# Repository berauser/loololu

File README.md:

# Dependencies

The project loolou depends on the avr-gcc and avrdude.

## Ubuntu

```
$ sudo apt-get install gcc-avr avrdude
```

# Build
## compile

```
$ make
```

## clean
```
$ make clean
```

## flash to attiny2313

```
# use default
# programmer: avrispv2
# usb device: /dev/ttyACM0
$ sudo make burn
```

```
# overwrite defaults
# AVRDUDE_PROGRAMMER override programmer type
# AVRDUDE_PORT overrides usb device
$ sudo make AVRDUDE_PROGRAMMER=avrispv2 AVRDUDE_PORT=/dev/ttyACM0 burn
```

## Useful links

* https://startingelectronics.org/tutorials/AVR-8-microcontrollers/ATtiny2313-tutorial/
* http://www.atmel.com/webdoc/avrlibcreferencemanual/index.html
* http://www.avr-tutorials.com/interrupts/avr-external-interrupt-c-programming

## Datasheet
### Attiny2313

* http://www.atmel.com/Images/Atmel-2543-AVR-ATtiny2313_Datasheet.pdf

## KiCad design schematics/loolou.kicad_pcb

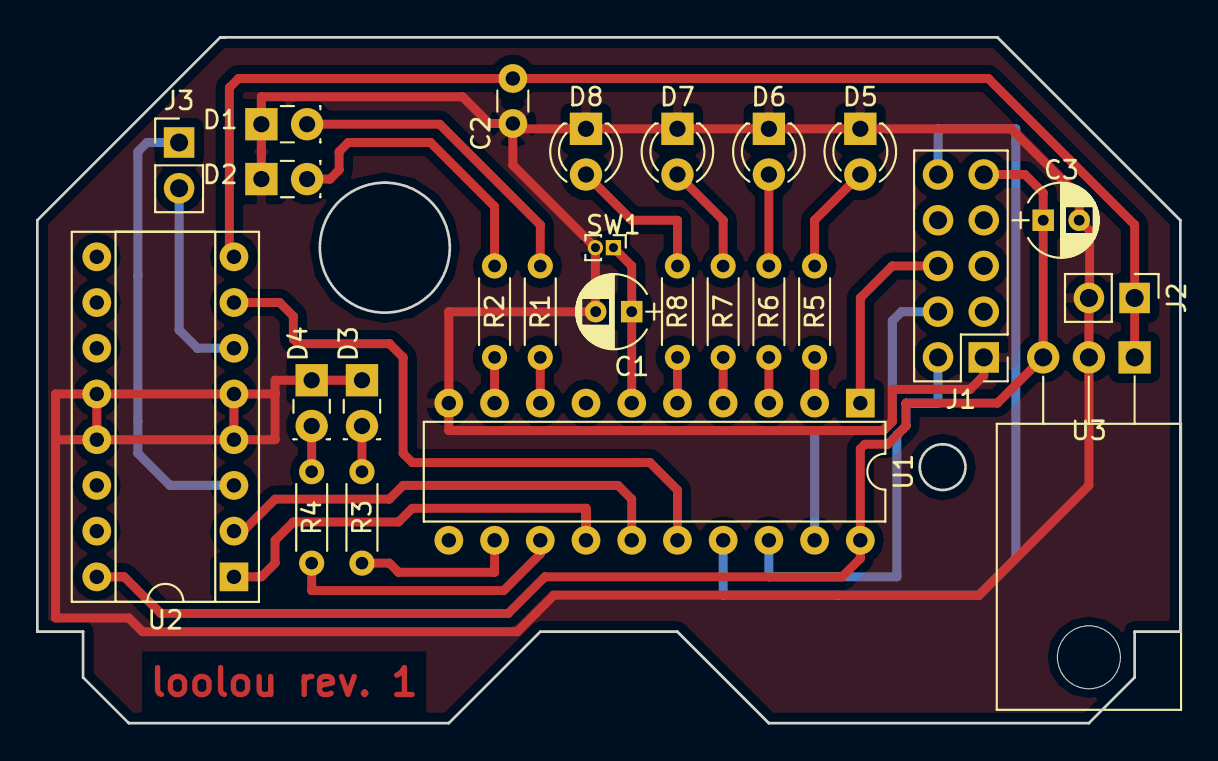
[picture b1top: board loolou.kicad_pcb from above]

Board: 2 copper layers, 63.5 x 38.1 mm, 26 parts (0 on the bottom side), 29 nets.

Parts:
C1, C3: 2,2uF; CP_Radial_D4.0mm_P2.00mm
C2: 0,1uF; C_Disc_D3.0mm_W1.6mm_P2.50mm
D1, D2, D3, D4: LED; LED_Rectangular_W3.9mm_H1.9mm
D5, D6, D7, D8: LED; LED_D3.0mm
J1: CONN_02X05; Pin_Header_Straight_2x05_Pitch2.54mm
J2, J3: Conn_01x02; Pin_Header_Straight_1x02_Pitch2.54mm
R1, R2, R3, R4: 68; R_Axial_DIN0204_L3.6mm_D1.6mm_P5.08mm_Horizontal
R5, R6, R7, R8: 120; R_Axial_DIN0204_L3.6mm_D1.6mm_P5.08mm_Horizontal
SW1: SW_Push; Pin_Header_Straight_1x02_Pitch1.00mm
U1: ATTINY2313-20PU; DIP-20_W7.62mm
U2: L293D; DIP-16_W7.62mm_Socket
U3: LF50CV; TO-220_Horizontal

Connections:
+9V: C2.1, J2.1, U2.8, U3.1
/BACKWARD: U1.16, U2.7
/BUTTON: C1.1, SW1.1, U1.6
/FORWARD: U1.15, U2.2
/LED_1: R5.1, U1.2
/LED_2: R6.1, U1.3
/LED_3: R7.1, U1.4
/LED_4: R8.1, U1.5
/LED_BLUE: R2.1, U1.9
/LED_GREEN: R3.1, U1.12
/LED_RED: R1.1, U1.8
/LED_YELLOW: R4.1, U1.13
/MISO: J1.2, U1.18
/MOSI: J1.10, U1.17
/MOTOR_A: J3.1, U2.3
/MOTOR_B: J3.2, U2.6
/PWM: U1.14, U2.1
/RESET: J1.6, U1.1
/SCK: J1.4, U1.19
GND: C1.2, C2.2, C3.2, D1.1, D2.1, D3.1, D4.1, D5.1, D6.1, D7.1, D8.1, J1.1, J2.2, SW1.2, U1.10, U2.4, U2.5, U2.12, U2.13, U3.2
unnamed: D1.2, R1.2
unnamed: D2.2, R2.2
unnamed: D3.2, R3.2
unnamed: D4.2, R4.2
unnamed: D5.2, R5.2
unnamed: D6.2, R6.2
unnamed: D7.2, R7.2
unnamed: D8.2, R8.2
VCC: C3.1, J1.9, U1.20, U2.16, U3.3

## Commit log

2017-08-18 change random speed calculation
2017-08-18 add simple readme
2017-10-27 change motor direction to fix the issue on the shematics
2017-10-27 add missing gitignore
2017-10-27 add defines; add comments
2017-10-27 add license file
2017-10-27 remove unused include
2017-10-27 improve readme
2017-11-05 optimize size
2017-11-05 fix F_CPU value; refactor interrupts/functions (use timer)
2017-11-05 move set timer to init
2017-11-05 add shematics and templates
2017-12-10 add documentation
2017-12-10 add small documentation
2017-12-11 update documentation
2017-12-11 update Makefile and some comments in the source file
2017-12-11 add aisler link to documentation
2017-12-18 improve docuemtation, refactor setup/init methods
2017-12-18 add datasheets
2017-12-19 add licence
2017-12-19 update license file
2017-12-19 update wrong link
